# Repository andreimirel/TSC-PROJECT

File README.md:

# OpenBook E-Reader - TSC PROJECT

## General description
  The OpenBook E-Reader is an open-source e-reader device offering a distraction-free reading experience with physical buttons and a minimalist interface. It features environmental sensors that provide real-time environmental data, a sustainable design, and extended battery life of at least one week. The device boasts a large e-paper display, slim ergonomic design, and USB-C connectivity for charging and data transfer. OpenBook supports wireless ebook downloads and emphasizes customizable hardware and software for the tech-savvy reader. It aims to serve avid readers who value open-source technology, customization options, and environmental awareness.

## Block Diagram

## Bill of Materials

| Qty | Value | Description | Manufacturer Part # | Mouser Link |
|-----|-------|-------------|----------------------|-------------|
| 1 | - | ESP32-C6 Module | ESP32-C6-WROOM-1-N8 | [Datasheet](https://www.mouser.co.uk/datasheet/2/891/Espressif_ESP32_C6_WROOM_1__Datasheet_V0_1_PRELIMI-3239987.pdf) |
| 1 | - | Environmental Sensor | BME688 | [Datasheet](https://www.mouser.co.uk/datasheet/2/783/bst_bme688_fl000-2307034.pdf) |
| 1 | - | Real Time Clock | DS3231SN# | [Datasheet](https://www.mouser.co.uk/datasheet/2/609/DS3231-3421123.pdf) |
| 1 | - | MicroSD Card Socket | 112A-TAAR-R03 ATTEND | [Datasheet](https://www.attend.com.tw/data/download/file/112A-TAAR-R03.rar) |
| 1 | - | USB Type-C Connector | USB4110-GF-A | [Datasheet](https://www.mouser.co.uk/datasheet/2/837/GCT_USB4110_Product_Drawing___20k_cycles-3455479.pdf) |
| 1 | - | FFC Connector | FH34SRJ-24S-0.5SH | [Datasheet](https://www.mouser.co.uk/datasheet/2/185/FH34SRJ_24S_0_5SH_99__CL0580_1255_6_99_2DDrawing_0-1615044.pdf) |
| 1 | - | Qwiic Connector | QWIIC_RIGHT_ANGLE | [Datasheet](https://www.mouser.co.uk/datasheet/2/813/Qwiic_Connector_Datasheet-1223982.pdf) |
| 1 | - | Li-Ion Charge Controller | MCP73831 | [Datasheet](https://www.mouser.co.uk/datasheet/2/268/MCP73831_Family_Data_Sheet_DS20001984H-3441711.pdf) |
| 1 | - | LDO Regulator | XC6220A331MR-G | [Datasheet](https://www.mouser.co.uk/datasheet/2/760/xc6220-3371556.pdf) |
| 1 | - | Fuel Gauge IC | MAX17048G+T10 | [Datasheet](https://www.mouser.co.uk/datasheet/2/609/MAX17048_MAX17049-3469099.pdf) |
| 1 | - | Voltage Detector | BD5229G-TR | [Datasheet](https://fscdn.rohm.com/en/products/databook/datasheet/ic/power/voltage_detector/bd52xxg-e.pdf) |
| 2 | 20V/4.2A | P-Channel MOSFET | DMG2305UX-7 | [Datasheet](https://www.diodes.com/assets/Datasheets/DMG2305UX.pdf) |
| 1 | - | N-Channel MOSFET | SI1308EDL-T1-GE3 | [Datasheet](https://www.vishay.com/doc?63399) |
| 15 | 10kΩ | Resistor | RR0402 | [Datasheet](https://www.mouser.com/ds/2/447/PYu-RC0402_51_RoHS_L_6_r-8721.pdf) |
| 8 | 100nF | Capacitor | CC0402 | [Datasheet](https://eu.mouser.com/datasheet/2/40/cx5r_KGM-3223198.pdf) |
| 10 | 1µF/50V | Capacitor | CC0402 | [Datasheet](https://eu.mouser.com/datasheet/2/40/cx5r_KGM-3223198.pdf) |
| 5 | 4.7µF | Capacitor | CC0402 | [Datasheet](https://eu.mouser.com/datasheet/2/40/cx5r_KGM-3223198.pdf) |
| 3 | - | Schottky Diode | MBR0530 | [Datasheet](https://www.onsemi.com/PowerSolutions/product.do?id=MBR0530T3G) |
| 6 | - | TVS Diode | PGB1010603MR | [Datasheet](https://www.littelfuse.com/assetdocs/pulseguard-esd-suppressors-pgb1-datasheet?assetguid=8a337998-d54d-466b-be4e-dc5bcd1f9321) |
| 1 | 100µF | Polarized Capacitor | CPOL-EUCT3528 | [Datasheet](https://www.mouser.co.uk/datasheet/2/396/mlcc02_e-1307760.pdf) |
| 1 | - | Inductor | 744043680 | [Datasheet](https://www.we-online.com/components/products/datasheet/744043680.pdf) |
| 1 | - | ESD Protection Diode | USBLC6-2SC6Y | [Datasheet](https://www.mouser.co.uk/datasheet/2/389/usblc6_2sc6y-1852505.pdf) |
| 2 | - | Schottky Diode | SD0805S020S1R0 | [Datasheet](https://www.mouser.co.uk/datasheet/2/40/schottky-3165252.pdf) |
| 1 | - | Supercapacitor | CPH3225A | [Datasheet](https://www.mouser.co.uk/datasheet/2/360/Seiko_Instruments_MicroBattery_E_20230330_2024Jan_-3561061.pdf) |
| 1 | - | Varistor | ESP32C6_VARISTOR_CT | [Datasheet](https://www.mouser.co.uk/datasheet/2/358/typ_PFMF-1275918.pdf) |
| 17 | - | Test Points | TPTP20R | [Datasheet](https://www.mouser.co.uk/datasheet/2/215/5265_5269-2935484.pdf) |
| 1 | - | Solder Jumper | SJ | [Datasheet](https://www.mouser.co.uk/datasheet/2/210/ASC_WR-3314721.pdf) |
| 1 | - | LED (Green) | ADAFRUIT_LEDCHIP-LED0603 | [Specs](https://www.3dcontentcentral.com/secure/download-model.aspx?catalogid=9481&id=681976) |
| 3 | - | Custom Buttons | BUTTON_CUSYOMV1 | - |

## Core Hardware Modules

### 1. Processing Unit
- **ESP32-C6-WROOM-1-N8**  
  - **Key Features**:
    - 160MHz RISC-V single-core processor
    - 512KB SRAM + 8MB external flash
    - Wi-Fi 6 (802.11ax) and Bluetooth 5 LE
    - Ultra-low-power modes (<5µA deep sleep)
  - **Functions**:
    - Manages all peripheral communication
    - Handles e-book rendering and UI operations
    - Processes environmental sensor data
    - Manages power states and battery charging

### 2. Display System
- **7.5" E-Paper Display (WSH-13187)**
  - **Specifications**:
    - 800×480 resolution, 8:1 contrast ratio
    - SPI interface (4-wire) @ 10MHz max
    - Partial refresh (<0.5s), full refresh (<1s)
    - 170° viewing angle
  - **Power Management**:
    - 0W power consumption when static
    - 120mW during refresh (active)

### 3. Environmental Sensing
- **BME688 Integrated Sensor**
  - **Measurement Capabilities**:
    - Temperature: ±1°C accuracy (0-65°C)
    - Humidity: ±3% RH (20-80% RH)
    - Pressure: ±1 hPa (300-1100 hPa)
    - Air Quality: VOC and eCO2 detection
  - **Interface**:
    - I2C @ 400kHz
    - 30s warm-up time for accurate readings
  - **Power Consumption**:
    - 2mA during active measurement
    - 0.5µA in sleep mode

### 4. Power Management System
| Component | Function | Specifications |
|-----------|----------|----------------|
| **2500mAh LiPo Battery** | Primary power source | 3.7V nominal, 2C discharge rate |
| **MCP73831** | Battery charging | 500mA max charge current, 4.2V regulation |
| **MAX17048** | Fuel gauge | ±1% voltage accuracy, I2C interface |
| **XC6220A331MR-G** | Voltage regulator | 3.3V @ 300mA, 50µA quiescent current |

### 5. User Interface Components
- **Tactile Buttons (3x)**
  - Panasonic EVQ-Q2A03W switches
  - 1M cycle lifespan
  - Hardware-debounced (RC filters)
- **LED Indicators**:
  - Charging status (red/green)
  - System activity (blue)

### 6. Connectivity
- **USB-C Port (Amphenol 12401641E4R)**
  - USB 2.0 Full Speed (12Mbps)
  - 5V/1A charging
  - ESD protection (USBLC6-2SC6Y)
- **Wi-Fi 6**:
  - 20MHz channel bandwidth
  - WPA3 security support
  - OTA update capability

### 7. Memory & Storage
| Component | Type | Capacity | Interface |
|-----------|------|----------|-----------|
| **W25Q512JVEIQ** | SPI Flash | 512Mb (64MB) | Quad-SPI @ 133MHz |
| **MicroSD Slot** | Expandable | Up to 1TB | SPI @ 25MHz |

## ESP32-C6 Pins

| ESP32-C6 Pin    | Component / Function  | Description and Reason for Use                                                                                                               |
|-----------------|-----------------------|----------------------------------------------------------------------------------------------------------------------------------------------|
| IO1 (SDA)     | I2C Bus               | Used for communication with the BME688 sensor, battery fuel gauge IC (MAX17048), and RTC (DS3231). I²C enables multiple devices on one bus. |
| IO2 (SCL)     | I2C Clock             | Provides the clock signal for the I²C bus, synchronizing data transfer between the ESP32-C6 and connected I²C devices.                      |
| IO5 (MISO)    | SPI (E-Paper)         | Master In Slave Out for the SPI interface with the E-Paper display; receives data from the display to the ESP32-C6.                         |
| IO6 (MOSI)    | SPI (E-Paper)         | Master Out Slave In for the SPI interface with the E-Paper display; sends data from the ESP32-C6 to the display.                            |
| IO7 (SCK)     | SPI Clock (E-Paper)   | Provides the clock signal for the SPI interface with the E-Paper display, synchronizing data transfer.                                      |
| IO8 (CS)      | Chip Select (E-Paper) | Selects the E-Paper display for SPI communication, allowing communication with a single SPI device at a time.                               |
| IO9           | E-Paper DC            | Data/Command control for the E-Paper display, indicating whether the transmitted data is command instructions or display data.              |
| IO10          | E-Paper RST           | Reset pin for the E-Paper display, used to initialize or reset the display.                                                                 |
| IO11          | E-Paper BUSY          | Busy status pin for the E-Paper display, indicating if the display is occupied and cannot receive new commands.                             |
| IO12          | BUTTON_BOOT           | Button to enter programming/bootload mode.                                                                                                  |
| IO13          | BUTTON_RESET          | Button for hardware reset of the ESP32-C6.                                                                                                  |
| IO14          | BUTTON_USER           | User-defined button for application interactions.                                                                                           |
| IO15          | MAX17048 ALERT        | Alert pin from the battery fuel gauge IC, signaling critical battery conditions.                                                            |
| GPIO16/TXD0   | USB D+                | Positive data line for the USB interface.                                                                                                   |
| GPIO17/RXD0   | USB D-                | Negative data line for the USB interface.                                                                                                   |
| IO18          | STATUS_LED            | Controls the status LED for visual indication of the device state.                                                                          |
| IO19          | SD Card CS            | Chip select for the SD card on the SPI interface.                                                                                           |
| IO20          | SD Card MISO          | Master In Slave Out for the SPI interface with the SD card; receives data from the SD card.                                                 |
| IO21          | SD Card MOSI          | Master Out Slave In for the SPI interface with the SD card; sends data to the SD card.                                                      |
| IO4           | SD Card CLK           | SPI clock for the SD card, synchronizing data transfer.                                                                                     |

###  Additional Details - ESP32-C6 Pins
  
  ####   I2C Interface
      The GPIO1 (SDA) and GPIO2 (SCL) pins are used for the I²C bus, connecting the ESP32-C6 to:
        - **BME688 Sensor:** For reading temperature, humidity, pressure, and air quality data.
        - **MAX17048:** For monitoring battery level.
        - **DS3231:** For real-time clock (RTC) functionality.
    
  ####   SPI Interface
      The GPIO5, GPIO6, GPIO7, and GPIO8 pins are dedicated to the SPI interface with the E-Paper display. This interface requires:
        - **MISO (GPIO5):** Receives data from the display.
        - **MOSI (GPIO6):** Transmits data to the display.
        - **SCK (GPIO7):** Synchronizes the data transfer.
        - **CS (GPIO8):** Selects the E-Paper display for communication.
    
  ####  User Buttons
      The GPIO12, GPIO13, and GPIO14 pins are connected to the user control buttons:
        - **GPIO12 (BUTTON_BOOT):** Enters programming/bootload mode.
        - **GPIO13 (BUTTON_RESET):** Resets the ESP32-C6.
        - **GPIO14 (BUTTON_USER):** Allows user-defined interactions.
    
  ####  USB
      GPIO16 and GPIO17 are used for the USB interface, facilitating data transfer and charging.
    
  ####  SD Card
      The GPIO19, GPIO20, GPIO21, and GPIO4 pins are used for the SPI interface with the SD card, enabling data storage and access.

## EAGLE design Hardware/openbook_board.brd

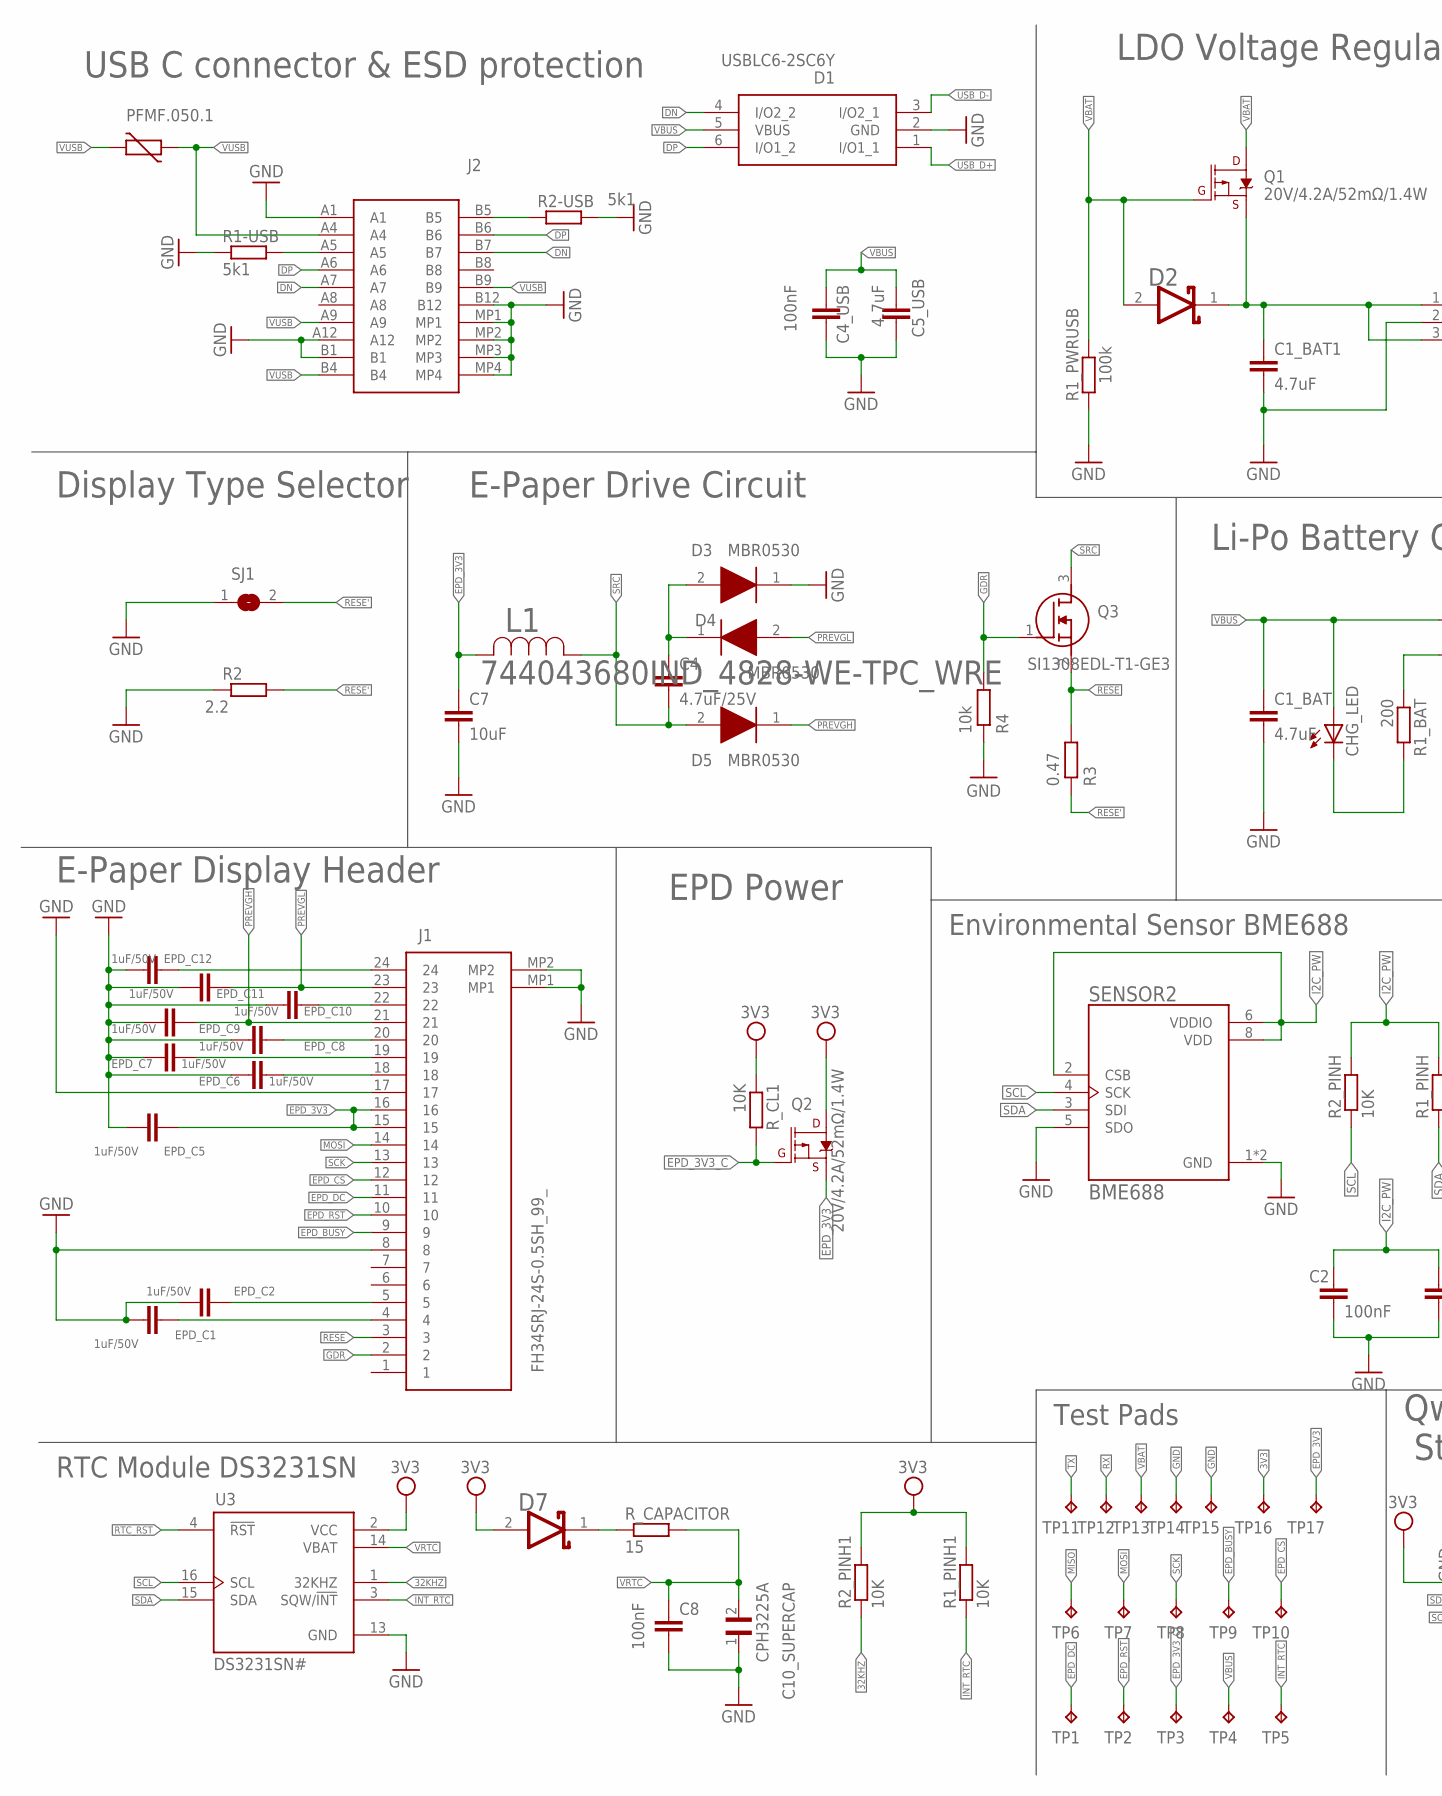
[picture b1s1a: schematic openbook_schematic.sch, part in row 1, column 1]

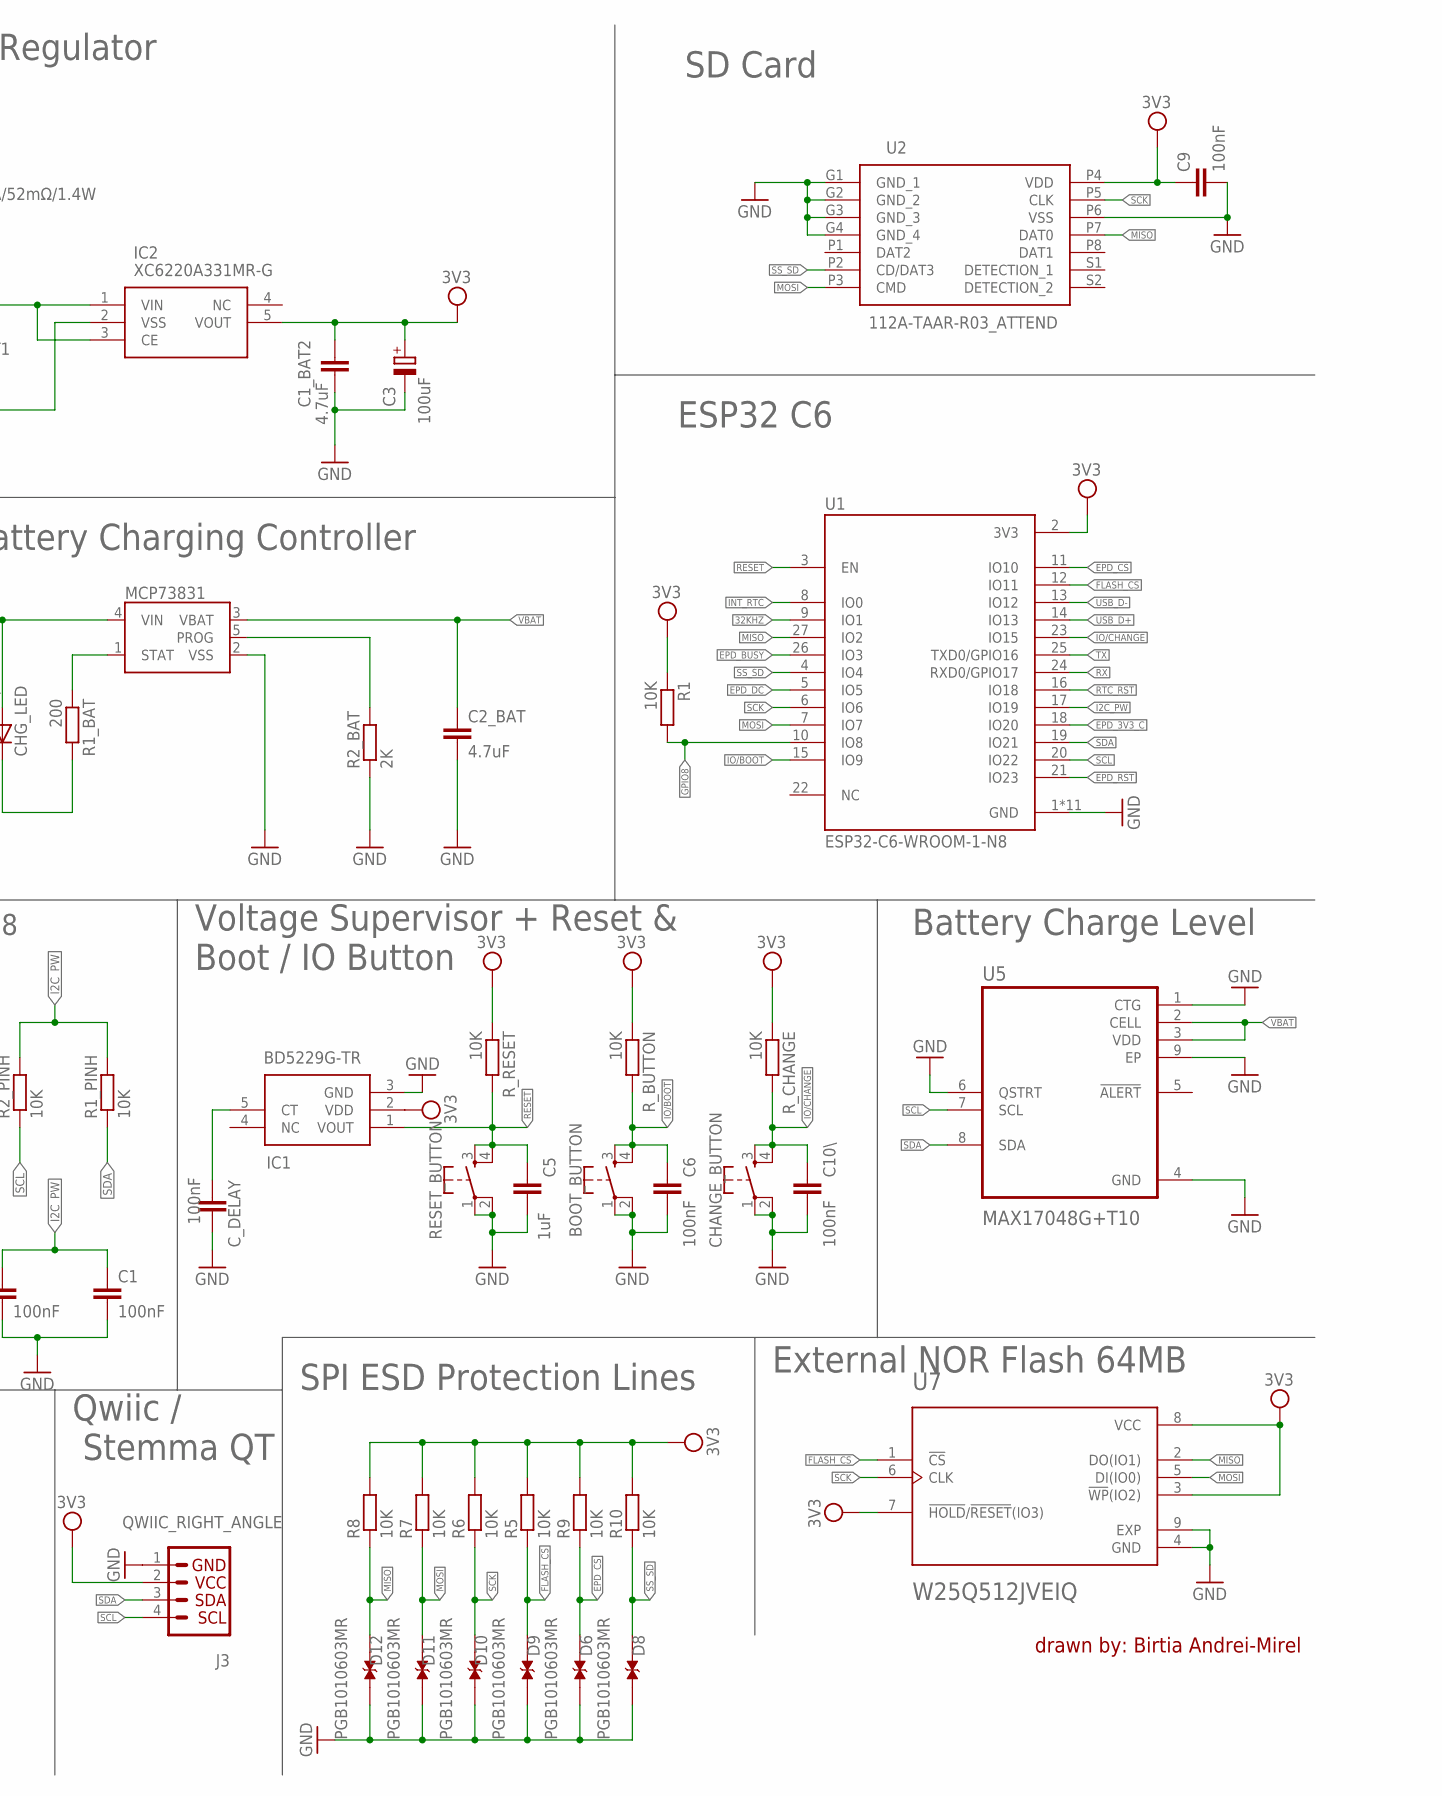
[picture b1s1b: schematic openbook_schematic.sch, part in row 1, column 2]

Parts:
BOOT_BUTTON: BUTTON_CUSYOMV1; MYBUTTON
C1, C2, C4_USB, C6, C8, C9, C10\: 100nF; EAGLE-LTSPICE_C0402
C1_BAT, C1_BAT1, C1_BAT2, C2_BAT, C5_USB: 4.7uF; EAGLE-LTSPICE_C0402
C3: 100uF; RCL_CT3528
C4: 4.7uF/25V; EAGLE-LTSPICE_C0402
C5: 1uF; EAGLE-LTSPICE_C0402
C7: 10uF; EAGLE-LTSPICE_C0402
C10_SUPERCAP: CPH3225A; CAPCP3225X100N
CHANGE_BUTTON: BUTTON_CUSYOMV1; MYBUTTON
CHG_LED: ADAFRUIT_LEDCHIP-LED0603; ADAFRUIT_CHIP-LED0603
C_DELAY: 100nF; EAGLE-LTSPICE_C0402
D1: USBLC6-2SC6Y; SOT95P280X145-6N
D2, D7: ESP32_WROVER_AVX---SD0805S020S1R0_AVX_SD0805S020S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; ESP32_WROVER_AVX---SD0805S020S1R0_AVX_SD0805S020S1R0_0
D3, D4, D5: MBR0530; SOD3716X135N
D6, D8, D9, D10, D11, D12: PGB1010603MR; DIOC1608X36N
EPD_C1, EPD_C2, EPD_C5, EPD_C6, EPD_C7, EPD_C8, EPD_C9, EPD_C10, EPD_C11, EPD_C12: 1uF/50V; EAGLE-LTSPICE_C0402
IC1: BD5229G-TR; SOT95P280X125-5N
IC2: XC6220A331MR-G; SOT95P280X120-5N
J1: FH34SRJ-24S-0.5SH_99_; FH34SRJ24S05SH99
J2: SAMACSYS_PARTS_USB4110-GF-A; SAMACSYS_PARTS_USB4110GFA
J3: QWIIC_RIGHT_ANGLE; JST04_1MM_RA
L1: 744043680IND_4828-WE-TPC_WRE; IND_4828-WE-TPC_WRE
MCP73831: ESP32_WROVER_SPARKFUN-IC-POWER_MCP73831; ESP32_WROVER_SPARKFUN-IC-POWER_SOT23-5
PFMF.050.1: ESP32C6_VARISTORCN1812; ESP32C6_VARISTOR_CT/CN1812
Q1, Q2: 20V/4.2A/52mΩ/1.4W; ESP32_WROVER_SPARKFUN-DISCRETESEMI_SOT23-3
Q3: SI1308EDL-T1-GE3; SOT65P210X110-3N
R1, R1_PINH, R1_PINH1, R2_PINH, R2_PINH1, R5, R6, R7, R8, R9, R10: 10K; ESP32_WROVER_EAGLE-LTSPICE_R0402
R1-USB, R2-USB: 5k1; ESP32_WROVER_EAGLE-LTSPICE_R0402
R1_BAT: 200; ESP32_WROVER_EAGLE-LTSPICE_R0402
R1_PWRUSB: 100k; ESP32_WROVER_EAGLE-LTSPICE_R0402
R2: 2.2; ESP32_WROVER_EAGLE-LTSPICE_R0402
R2_BAT: 2K; ESP32_WROVER_EAGLE-LTSPICE_R0402
R3: 0.47; ESP32_WROVER_EAGLE-LTSPICE_R0402
R4: 10k; ESP32_WROVER_EAGLE-LTSPICE_R0402
RESET_BUTTON: BUTTON_CUSYOMV1; MYBUTTON
R_BUTTON: 10K; ESP32_WROVER_EAGLE-LTSPICE_R0402
R_CAPACITOR: 15; ESP32_WROVER_EAGLE-LTSPICE_R0402
R_CHANGE: 10K; ESP32_WROVER_EAGLE-LTSPICE_R0402
R_CL1: 10K; ESP32_WROVER_EAGLE-LTSPICE_R0402
R_RESET: 10K; ESP32_WROVER_EAGLE-LTSPICE_R0402
SENSOR2: BME688; ESP32_WROVER_BME680_PSON80P300X300X100-8N
SJ1: SJ
TP1, TP2, TP3, TP4, TP5, TP6, TP7, TP8, TP9, TP10, TP11, TP12, TP13, TP14, TP15, TP16, TP17: TPTP20R; TP20R
U1: ESP32-C6-WROOM-1-N8; XCVR_ESP32-C6-WROOM-1-N8
U2: 112A-TAAR-R03_ATTEND; 112ATAARR03ATTEND
U3: DS3231SN#; SOIC127P1032X265-16N
U5: MAX17048G+T10; SON50P200X200X80-9N
U7: W25Q512JVEIQ; SON127P600X800X80-9N

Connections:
3V3: C1_BAT2.1, C3.+, C9.1, D7.2 (ANODE), IC1.2 (VDD), IC2.5 (VOUT), J3.2, Q2.3 (D), R1.1, R1_PINH1.2, R2_PINH1.2, R5.2, R6.2, R7.2, R8.2, R9.2, R10.2, R_BUTTON.1, R_CHANGE.1, R_CL1.1, R_RESET.1, TP16.TP, U1.2 (3V3), U2.P4 (VDD), U3.2 (VCC), U7.3 (!WP!(IO2)), U7.7 (!HOLD!/!RESET!(IO3)), U7.8 (VCC)
32KHZ: R2_PINH1.1, U1.9 (IO1), U3.1 (32KHZ)
DN: D1.4 (I/O2_2), J2.A7, J2.B7
DP: D1.6 (I/O1_2), J2.A6, J2.B6
EPD_3V3: C7.1, EPD_C5.1, J1.15, J1.16, L1.2, Q2.2 (S), TP17.TP
EPD_3V3_C: Q2.1 (G), R_CL1.2, TP3.TP, U1.18 (IO20)
EPD_BUSY: J1.9, TP9.TP, U1.26 (IO3)
EPD_CS: D6.1, J1.12, R9.1, TP10.TP, U1.11 (IO10)
EPD_DC: J1.11, TP1.TP, U1.5 (IO5)
EPD_RST: J1.10, TP2.TP, U1.21 (IO23)
FLASH_CS: D9.1, R5.1, U1.12 (IO11), U7.1 (!CS)
GDR: J1.2, Q3.1 (G), R4.2
GND: BOOT_BUTTON.1, BOOT_BUTTON.2, C1.2, C1_BAT.2, C1_BAT1.2, C1_BAT2.2, C2.2, C2_BAT.2, C3.-, C4_USB.2, C5.2, C5_USB.2, C6.2, C7.2, C8.2, C9.2, C10\.2, C10_SUPERCAP.1, CHANGE_BUTTON.1, CHANGE_BUTTON.2, C_DELAY.2, D1.2 (GND), D3.1 (K), D6.2, D8.2, D9.2, D10.2, D11.2, D12.2, EPD_C1.2, EPD_C2.2, EPD_C5.2, EPD_C6.2, EPD_C7.2, EPD_C8.2, EPD_C9.2, EPD_C10.2, EPD_C11.2, EPD_C12.2, IC1.3 (GND), IC2.2 (VSS), J1.8, J1.17, J1.MP1, J1.MP2, J2.A1, J2.A12, J2.B1, J2.B12, J2.MP1, J2.MP2, J2.MP3, J2.MP4, J3.1, MCP73831.2 (VSS), R1-USB.1, R1_PWRUSB.1, R2.1, R2-USB.2, R2_BAT.1, R4.1, RESET_BUTTON.1, RESET_BUTTON.2, SENSOR2.1 (GND), SENSOR2.5 (SDO), SENSOR2.7 (GND), SJ1.1, TP14.TP, TP15.TP, U1.1 (GND), U1.28 (GND), U1.29_1 (GND), U1.29_2 (GND), U1.29_3 (GND), U1.29_4 (GND), U1.29_5 (GND), U1.29_6 (GND), U1.29_7 (GND), U1.29_8 (GND), U1.29_9 (GND), U2.G1 (GND_1), U2.G2 (GND_2), U2.G3 (GND_3), U2.G4 (GND_4), U2.P6 (VSS), U3.13 (GND), U5.1 (CTG), U5.4 (GND), U5.6 (QSTRT), U5.9 (EP), U7.4 (GND), U7.9 (EXP)
GPIO8: R1.2, U1.10 (IO8)
I2C_PW: C1.1, C2.1, R1_PINH.2, R2_PINH.2, SENSOR2.2 (CSB), SENSOR2.6 (VDDIO), SENSOR2.8 (VDD), U1.17 (IO19)
INT_RTC: R1_PINH1.1, TP5.TP, U1.8 (IO0), U3.3 (SQW/!INT)
IO/BOOT: BOOT_BUTTON.3, BOOT_BUTTON.4, C6.1, R_BUTTON.2, U1.15 (IO9)
IO/CHANGE: C10\.1, CHANGE_BUTTON.3, CHANGE_BUTTON.4, R_CHANGE.2, U1.23 (IO15)
MISO: D12.1, R8.1, TP6.TP, U1.27 (IO2), U2.P7 (DAT0), U7.2 (DO(IO1))
MOSI: D11.1, J1.14, R7.1, TP7.TP, U1.7 (IO7), U2.P3 (CMD), U7.5 (DI(IO0))
unnamed: J2.B5, R2-USB.1
unnamed: J2.A5, R1-USB.2
unnamed: MCP73831.5 (PROG), R2_BAT.2
unnamed: EPD_C2.1, J1.5
unnamed: C1_BAT1.1, D2.1 (CATHODE), IC2.1 (VIN), IC2.3 (CE), Q1.2 (S)
unnamed: MCP73831.1 (STAT), R1_BAT.1
unnamed: C4.1, D3.2 (A), D4.1 (K)
unnamed: CHG_LED.C, R1_BAT.2
unnamed: EPD_C1.1, J1.4
unnamed: EPD_C12.1, J1.24
unnamed: C_DELAY.1, IC1.5 (CT)
unnamed: EPD_C10.1, J1.22
unnamed: D7.1 (CATHODE), R_CAPACITOR.1
unnamed: EPD_C8.1, J1.20
unnamed: EPD_C7.1, J1.19
unnamed: EPD_C6.1, J1.18
PREVGH: D5.1 (K), EPD_C9.1, J1.21
PREVGL: D4.2 (A), EPD_C11.1, J1.23
RESE: J1.3, Q3.2 (S), R3.2
RESE': R2.2, R3.1, SJ1.2
RESET: C5.1, IC1.1 (VOUT), RESET_BUTTON.3, RESET_BUTTON.4, R_RESET.2, U1.3 (EN)
RTC_RST: U1.16 (IO18), U3.4 (!RST)
RX: TP12.TP, U1.24 (RXD0/GPIO17)
SCK: D10.1, J1.13, R6.1, TP8.TP, U1.6 (IO6), U2.P5 (CLK), U7.6 (CLK)
SCL: J3.4, R2_PINH.1, SENSOR2.4 (SCK), U1.20 (IO22), U3.16 (SCL), U5.7 (SCL)
SDA: J3.3, R1_PINH.1, SENSOR2.3 (SDI), U1.19 (IO21), U3.15 (SDA), U5.8 (SDA)
SRC: C4.2, D5.2 (A), L1.1, Q3.3 (D)
SS_SD: D8.1, R10.1, U1.4 (IO4), U2.P2 (CD/DAT3)
TX: TP11.TP, U1.25 (TXD0/GPIO16)
USB_D+: D1.1 (I/O1_1), U1.14 (IO13)
USB_D-: D1.3 (I/O2_1), U1.13 (IO12)
VBAT: C2_BAT.1, D2.2 (ANODE), MCP73831.3 (VBAT), Q1.1 (G), Q1.3 (D), R1_PWRUSB.2, TP13.TP, U5.2 (CELL), U5.3 (VDD)
VBUS: C1_BAT.1, C4_USB.1, C5_USB.1, CHG_LED.A, D1.5 (VBUS), MCP73831.4 (VIN), TP4.TP
VRTC: C8.1, C10_SUPERCAP.2, R_CAPACITOR.2, U3.14 (VBAT)
VUSB: J2.A4, J2.A9, J2.B4, J2.B9, PFMF.050.1.1, PFMF.050.1.2

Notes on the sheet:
USB C connector & ESD protection
LDO Voltage Regulator
SD Card
ESP32 C6
Li-Po Battery Charging Controller
E-Paper Drive Circuit
Display Type Selector
E-Paper Display Header
EPD Power
Environmental Sensor BME688
Voltage Supervisor + Reset & Boot / IO Button
Battery Charge Level
External NOR Flash 64MB
SPI ESD Protection Lines
Qwiic / Stemma QT
Test Pads
RTC Module DS3231SN
drawn by: Birtia Andrei-Mirel

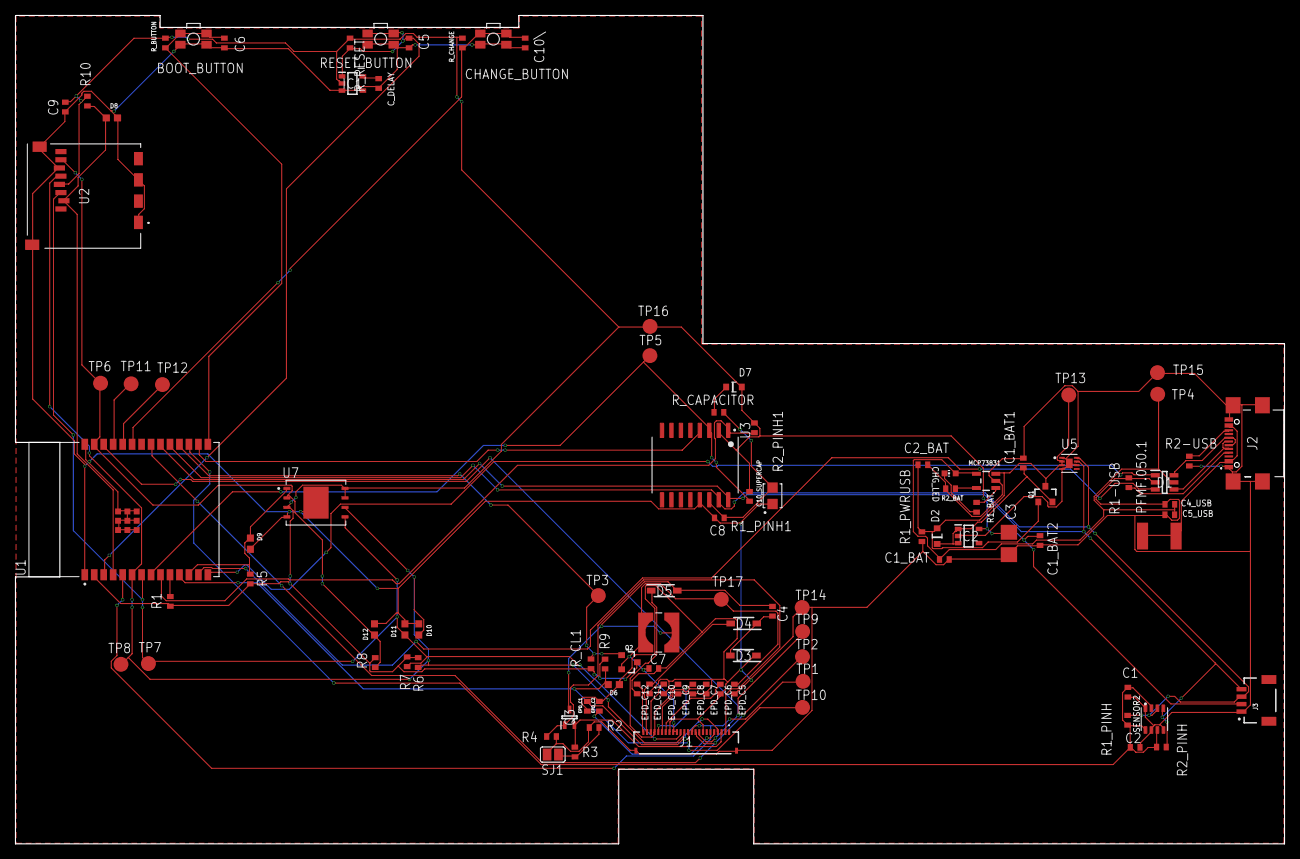
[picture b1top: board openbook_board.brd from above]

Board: 2 copper layers, 170.2 x 111.1 mm, 103 parts (0 on the bottom side), 55 nets.

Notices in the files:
parts and their libraries:
COPYRIGHT: Copyright (C) 2024 Ultra Librarian. All rights reserved.
